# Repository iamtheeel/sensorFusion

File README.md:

# sensorFusion
A system to increase grip strength based on computer vision and myoelectric sensing.

The computer vision system is in [CV](./cv "Python Based Computer Vision using YOLO")

To install the code:
> git clone https://github.com/iamtheeel/sensorFusion.git

Then follow the directions in each subsystem

Note: 
Instructions on setting up the corel board are in the [running](./running "Real Time") Subsection

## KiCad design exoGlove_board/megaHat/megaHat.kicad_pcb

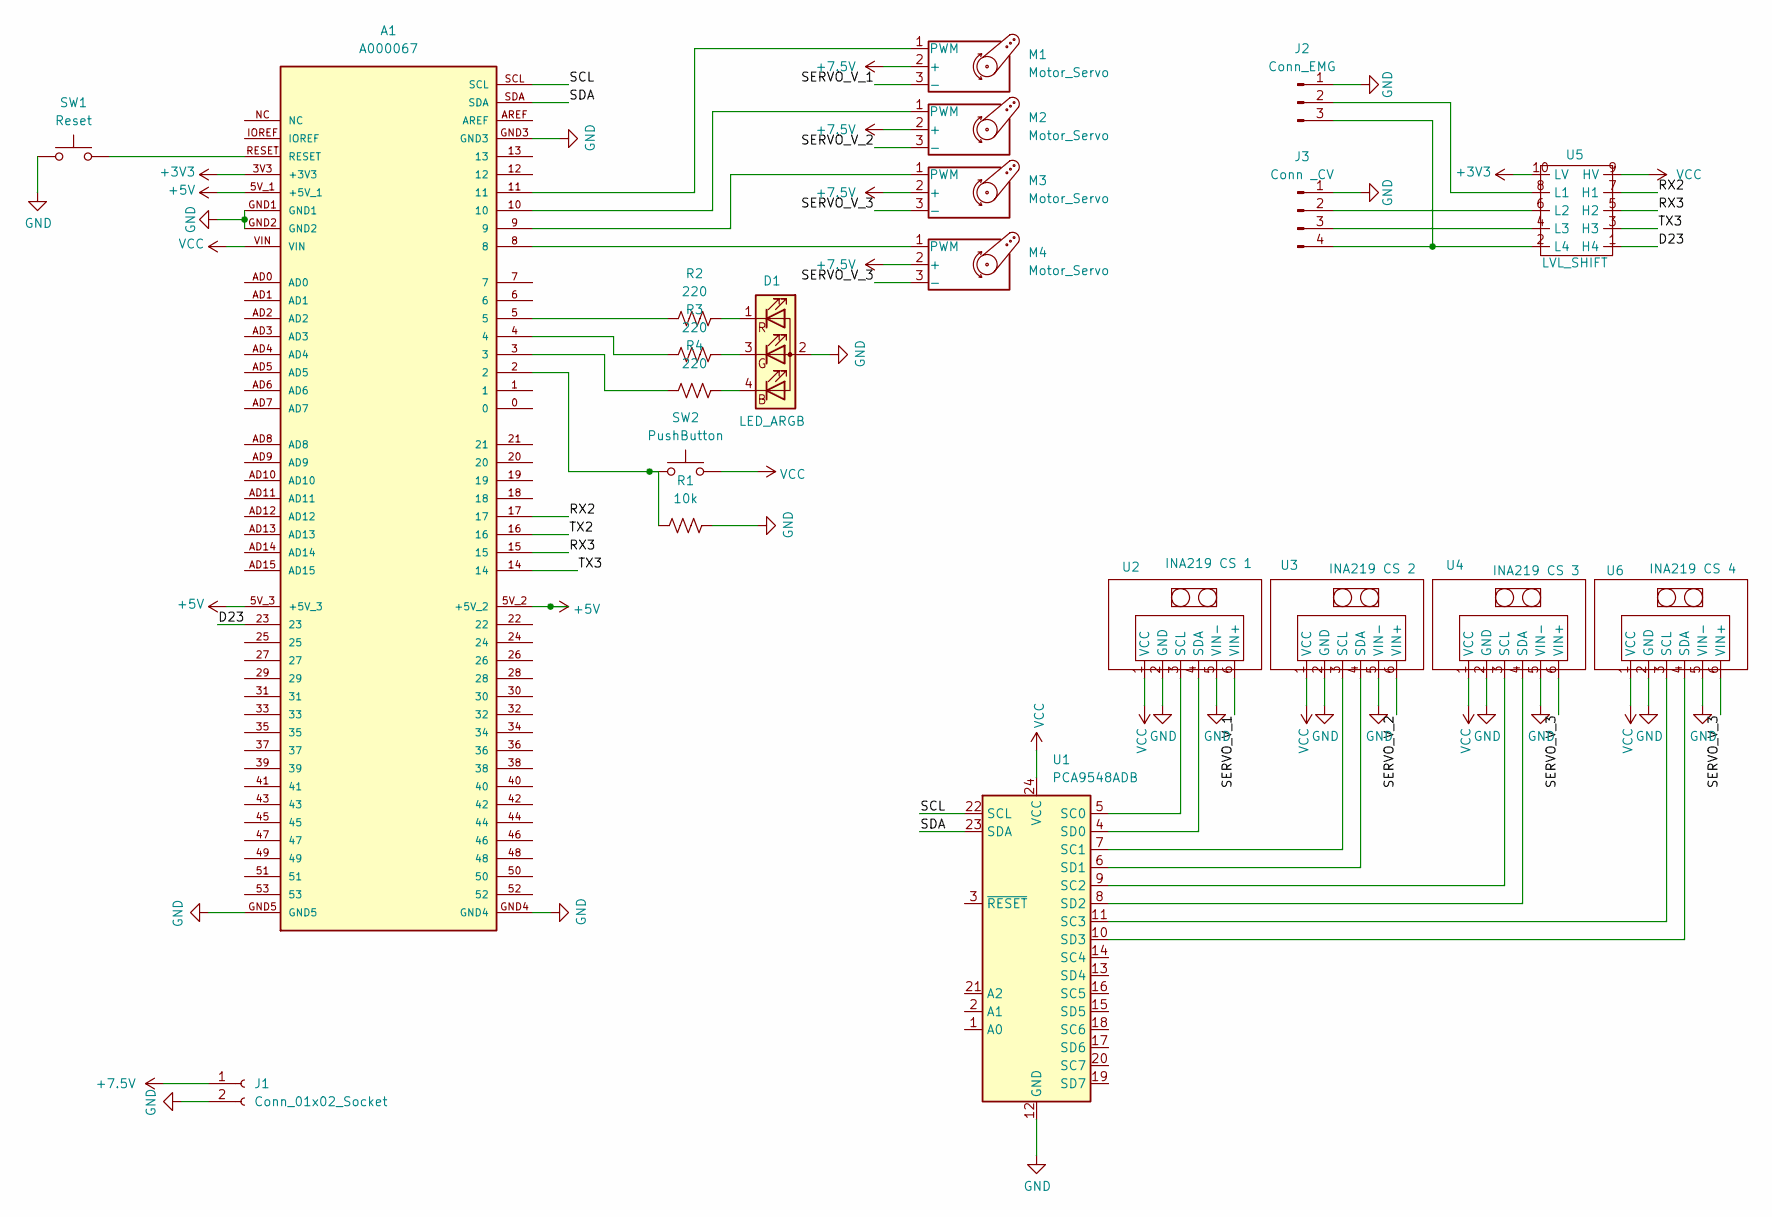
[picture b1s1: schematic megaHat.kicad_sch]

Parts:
A1: A000067; MODULE_A000067; PARTREV 3
D1: LED_ARGB; LED_D5.0mm-4_RGB_Staggered_Pins
J1: Conn_01x02_Socket; TerminalBlock_Phoenix_MKDS-1,5-2_1x02_P5.00mm_Horizontal
J2: Conn_EMG; PinHeader_1x03_P2.54mm_Vertical
J3: Conn _CV; PinHeader_1x04_P2.54mm_Vertical
M1, M2, M3, M4: Motor_Servo; PinHeader_1x03_P2.54mm_Vertical
R1: 10k; R_Axial_DIN0204_L3.6mm_D1.6mm_P2.54mm_Vertical
R2, R3, R4: 220; R_Axial_DIN0204_L3.6mm_D1.6mm_P2.54mm_Vertical
SW1: Reset; SW_PUSH_6mm
SW2: PushButton; SW_PUSH_6mm
U1: PCA9548ADB; TCA9548A_MultiplexerBreakout
U2: INA219 CS 1; PinHeader_1x06_P2.54mm_Vertical
U3: INA219 CS 2; PinHeader_1x06_P2.54mm_Vertical
U4: INA219 CS 3; PinHeader_1x06_P2.54mm_Vertical
U5: LVL_SHIFT; Pololu-LLShift_2595
U6: INA219 CS 4; PinHeader_1x06_P2.54mm_Vertical

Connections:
+3V3: A1.3V3 (+3V3), U5.10 (LV)
+5V: A1.5V_1 (+5V_1), A1.5V_2 (+5V_2), A1.5V_3 (+5V_3)
+7.5V: J1.1, M1.2 (+), M2.2 (+), M3.2 (+), M4.2 (+)
/D23: A1.23, U5.1 (H4)
/RX2: A1.17, U5.7 (H1)
/RX3: A1.15, U5.5 (H2)
/SCL: A1.SCL, U1.22 (SCL)
/SDA: A1.SDA, U1.23 (SDA)
/SERVO_V_1: M1.3 (-), U2.6 (VIN+)
/SERVO_V_2: M2.3 (-), U3.6 (VIN+)
/SERVO_V_3: M3.3 (-), M4.3 (-), U4.6 (VIN+), U6.6 (VIN+)
/TX2: A1.16
/TX3: A1.14, U5.3 (H3)
GND: A1.GND1, A1.GND2, A1.GND3, A1.GND4, A1.GND5, D1.2 (A), J1.2, J2.1, J3.1, R1.2, SW1.1, U1.12 (GND), U2.2 (GND), U2.5 (VIN-), U3.2 (GND), U3.5 (VIN-), U4.2 (GND), U4.5 (VIN-), U6.2 (GND), U6.5 (VIN-)
unnamed: A1.2, R1.1, SW2.1
unnamed: A1.3, R4.1
unnamed: A1.4, R3.1
unnamed: A1.5, R2.1
unnamed: A1.RESET, SW1.2
unnamed: D1.4 (BK), R4.2
unnamed: D1.3 (GK), R3.2
unnamed: D1.1 (RK), R2.2
unnamed: J2.2, U5.8 (L1)
unnamed: J2.3, J3.4, U5.2 (L4)
unnamed: J3.2, U5.6 (L2)
unnamed: J3.3, U5.4 (L3)
unnamed: A1.11, M1.1 (PWM)
unnamed: A1.10, M2.1 (PWM)
unnamed: A1.9, M3.1 (PWM)
unnamed: A1.8, M4.1 (PWM)
unnamed: U1.5 (SC0), U2.3 (SCL)
unnamed: U1.7 (SC1), U3.3 (SCL)
unnamed: U1.9 (SC2), U4.3 (SCL)
unnamed: U1.11 (SC3), U6.3 (SCL)
unnamed: U1.4 (SD0), U2.4 (SDA)
unnamed: U1.6 (SD1), U3.4 (SDA)
unnamed: U1.8 (SD2), U4.4 (SDA)
unnamed: U1.10 (SD3), U6.4 (SDA)
VCC: A1.VIN, SW2.2, U1.24 (VCC), U2.1 (VCC), U3.1 (VCC), U4.1 (VCC), U5.9 (HV), U6.1 (VCC)

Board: 2 copper layers, 21 parts (0 on the bottom side), 38 nets, no tracks yet.

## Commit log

2024-06-11 First light
2024-06-11 Added train line
2024-06-12 Got a model to 603kB
2024-06-13 YOLO V8 install on Spresense... non-functional, but installed and doing inference
2024-06-14 Viewer to look at training/validation/test images and lables Prepairing for converting pior data to YOLO format
2024-06-15 Viewer works with ssd labels. Viewer has single image mode
2024-06-15 Cleaned up getThisImgLabs
2024-06-15 Added headder
2024-06-15 Box color by label text
2024-06-16 Fixed new window for each image bug
2024-06-21 work
2024-06-24 Rebuilt env, runs on laptop
2024-06-27 Experimenting
2024-06-27 Moar Exp
2024-07-06 Device info
2024-07-06 Added Apple silicon to device test
2024-07-06 improved device selection
2024-07-07 Fixed lable convert issue. New line missing
2024-07-07 config change
2024-07-07 Added
2024-07-08 Sorted out export errors
2024-07-08 added tpu to export
2024-07-08 Aded model
2024-07-08 notes on devboard
2024-07-26 First push on distance calc, and calc viewer
2024-07-26 Reset vars at load data
2024-07-26 Fixed issue with distance.loadData where nonHand images went through
2024-07-26 Moar variable re-init
2024-07-27 Added confidence to image display
2024-07-27 Adjusted font
2024-07-27 added multi hand handeling
2024-07-29 Noodeling about
2024-07-29 laptop changes
2024-07-29 re-arranging files
2024-08-02 Looking at image sizes
2024-08-03 Set up readme, install, requirements
2024-08-03 Set up some dir structure. Add pre-trained model to runImage
2024-08-03 Transfer learning
2024-08-03 installer stuff
2024-08-04 Transfer learning and full training
2024-08-04 distance now takes argument for what class number is the hand (80)
2024-08-08 Sorting for file export
2024-08-08 Trying to run in the lab.
2024-08-09 Added the edgetpu runtime files from https://github.com/jveitchmichaelis/edgetpu-yolo
2024-08-09 added dataset config file
2024-08-10 Running our model on the TPU.
2024-08-10 Augmentation to training
2024-08-10 getting ready for merge
2024-08-10 Prep for getting YOLO and TPU results in same format
2024-08-10 merging
2024-08-10 cleaning up results hand off to distance
2024-08-10 Got display working on TPU
2024-08-10 Exporting
2024-08-10 Drawing the screen when we don't have a hand/object combiniation Full screen
2024-08-10 Added config for full screen Fixed center bug if we don't have a hand
2024-08-10 Running new model with hsv_h, sees apples!
2024-08-10 Quit from cv2 works now.
2024-08-10 changed class count
2024-08-11 moved logging setup out of TPU specific
2024-08-11 logging
2024-08-11 githell
2024-08-11 Run works with 81 class train
2024-08-11 Added configuration file
2024-08-11 Refactored a bit. Continuous webcam, webcam displays results
2024-08-12 Added frame rate config
2024-08-12 Added flag on webcam to just run once
2024-08-13 details
2024-08-13 WebCam working on TPU. Also, cleaned up a little
2024-08-13 Cleanup a orphened variable`
2024-08-13 Trying to get the window full size. Works on the mac, not on the TPU... Sigh.
2024-08-14 Clean up
2024-08-14 Trying to get full size full screen image to work
2024-08-14 config for export
2024-08-14 working
2024-08-14 NMS settings. Got multiple overlaping objects working
2024-08-14 Window sizing, full screen now works
2024-08-15 Fixed coco_withHand.yaml, was pointing at data that was tagged 0,1
2024-08-15 moar fix
2024-08-15 Logger and config for trainer
2024-08-15 Export did not need to be a function, was redundant and silly
2024-08-15 Export log and config. Exported 640px model
2024-08-16 config
2024-08-23 Working on documentation
2024-08-23 typo
2024-08-23 moar doc
2024-08-23 working on cv doc
2024-08-23 Added training set aka: git, i keel u
2024-08-23 Addeed training doc
2024-08-23 Don't need that anymore
2024-08-23 Update README.md: configuration
2024-08-23 run for docwriting
2024-08-23 working on doc
2024-08-23 addeding doc for runtime
2024-08-23 Prep for doc writing
2024-08-23 added some images for readme
2024-08-26 added image
2024-08-26 Update README.md (terminal)
2024-08-26 Update README.md (OS Install)
2024-08-26 Update README.md (software install)
2024-08-27 Update README.md network
2024-08-27 Update README.md (spealing)
2024-08-27 Update README.md (X11... er wayland, or weston. whatever GUI)
2024-08-27 Update README.md (ssh)
2024-08-28 Update README.md (contents)
2024-08-28 Update README.md (running)
2024-09-04 documentation
2024-09-04 when will I learn to push at the end of a run?
2024-09-04 Starting GPIO aka Servo
2024-09-04 moved config to root added config and log to servo
2024-09-04 Basic servo timing. Not good presision tho, what is wrong?
2024-09-04 GPIO and PWM servo proof of concept
2024-09-06 moved configs
2024-09-06 Oh git!
2024-09-06 modifyed running to run in dir
2024-09-06 Work on glasses
2024-09-09 Trying to get the glasses to work well
2024-09-12 Got glasses working. Added a check to see if the buffer was full. Needs to be prityer tho
2024-09-12 Put camera into seperate file and function
2024-09-16 Added thread, reversed image size h,w for cv2
2024-09-16 Finished puting the glasses stream in a thread. Also added crop
2024-09-16 Added a restart on bad camera grab.
2024-09-16 Running on TPU and cleaning up logging a bit
2024-09-16 Documented img resize some
2024-09-17 Minor tweek to camera restart
2024-09-23 Got the servo driver to function.
2024-09-23 Added PWM Driver DOc
2024-09-23 Servo to 90ccw, then 90cw. Tested with actual servo Note: Clock time is waaaay off, by like 0.2uS
2024-09-23 making into object and funtions
2024-09-23 Works!
2024-09-23 Final polish on the demo loop
2024-09-23 Tested multi servo, and reserected the bad board
2024-09-23 What did I change?
2024-09-26 Working directly on glove
2024-09-26 Remove the 100ms delay on write... oops.
2024-09-26 Aded input to ask what position to put the servo in
2024-09-26 Testing sending multiple registers at the same time
2024-10-02 8 Class
2024-10-03 renamed 8 to 7
2024-10-03 moe more
2024-10-03 asdf
2024-10-03 I seem to have missed an important file
2024-10-17 Added to python version note
2024-10-27 training v8 and v11
2024-10-28 Starting work on data capture
2024-10-28 Got single camera image saves working
2024-10-29 RUnning in the lab
2024-11-05 moved inf to debugs Got multi cameras working Todo: quit, save, timing
2024-11-06 Finished multi-camera... well, for 2 cameras anyway
2024-11-20 Minor tweeks
2025-02-03 Colecing data?
2025-02-03 Sigh
2025-02-03 Clock reset on GPIO: Untested
2025-02-03 Small change to image echo
2025-02-07 Fixed a couple of bugs in Image Capture Time
2025-02-07 Fixed glasses aspect ratio
2025-02-21 TimeSync: Set the pin I want and set to pullup
2025-02-26 I r dumb, what did I do?
2025-03-05 Work on datacap and lableing
2025-03-05 script to count labels
2025-03-07 Calibration, enbigend the distance text on the display
2025-03-10 Got files working again. Also, reports the name of the object, and color codes the bounding box.
2025-03-10 Training sessh
2025-03-12 Running for the week
2025-03-12 Cleaning up
2025-03-17 Added serial... Needs testing
2025-03-17 Serial comms tested
2025-03-17 Clarifying comments
2025-03-17 Training
2025-03-17 Day 2 cam 1 fully lab
2025-03-19 Train for new version of UL
2025-03-19 Added the new dataset
2025-03-19 Syncing
2025-03-19 Setup for running on laptop
2025-03-21 Config for run
2025-03-21 Syncing up
2025-03-21 Export
2025-03-21 I will be better
2025-03-21 Fighting with git
2025-03-21 Running on the TPU
2025-03-21 Everything works on the TPU!
2025-03-22 Added file save
2025-05-06 Save video of output
2025-05-06 Video save settings to match camera settings
2025-05-08 Added circut board
2025-05-23 Moving the board to its own repository
2025-05-30 Saves logfile and video based on run name
2025-05-30 Crash fixed??
2025-06-13 Oscar did what? And fixed typo on log rename
2025-06-15 deleted readme?
2025-06-15 Cleaned up capImage, also spealing errors... Sigh.
2025-06-16 Comented out the serial port none
2025-06-16 working on crash
2025-06-17 still hanging
2025-06-17 Tilting windmills
2025-06-17 Do inference as a worker that we can restart
2025-06-17 Chat bot fix for thread not being started yet
2025-06-17 Input tensor
2025-06-17 fix on return, added err.txt
2025-06-17 redoing the worker loop
2025-06-17 fix 45784232
2025-06-17 new error
2025-06-17 changed the worker loop
2025-06-18 modifyed err
2025-06-18 I have to move allocate_tensors() to the new stauff
2025-06-18 Worker version working. Also found the mem double tap!
2025-06-18 Exit works, timeout to 1s
2025-06-18 Final cleanup on TPU crash issue, timeout is a config item
2025-06-19 twiddels while writing docs
2025-07-04 Setup for yolo11
2025-07-04 Don't save weights in git
2025-07-05 Training for yolo11
2025-07-09 feat: Add Raspberry Pi 5 support with automatic platform detection
    - Add RaspberryPiModel for ARM-optimized inference (TFLite/ONNX)
    - Implement automatic device detection (TPU/Raspberry Pi/Desktop)
    - Add setup scripts, test suite, and comprehensive documentation
    - Maintain full backward compatibility with existing TPU functionality
    - Enable cost-effective deployment on Raspberry Pi 5 (2.5-6.7 FPS)
    New files: rpiModel.py, requirements_rpi.txt, setup_rpi.sh, test_rpi.py, README_RaspberryPi.md
